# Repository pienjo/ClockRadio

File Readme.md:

This is just a simple alarm clock.

How to use
==========

## Main display

A short press on the mode button rotates between the following modes:

  * Time. The first 2 columns of the LED display are used for a Day-of-week indicator; monday is at the first row.
  * Date
  * Alarm 1.  
  * Alarm 2. 
  * One-time alarm

A long press on the mode button will edit whatever is being displayed (time,
alarm 1, alarm 2, or one-time alarm). Performing a long press while the
date is being shown will edit the time drift compensation. The display will
return to ''Time'' when no buttons are pressed.

## Display brightness

The display has separate brightness settings for day and night. Transition 
from day to night occurs roughly around sunrise (Assuming a northern 
lattitude of aroudn 51 degrees). 

Brightness can be changed using the ''increase'' and ''decrease'' buttons while the 
display is showing the time.

## Daylight saving time

The clock will automatically apply daylight saving time, based on the current (2019) 
EU rules (which are bound to change again, oh well)

## Editing

A short press on the mode button will advance to the next digit/number. Use 
the increment/decrement buttons to change digits/numbers. A long press
on the mode button will abort the edit.

## Radio

Pressing the on/off button will toggle the radio. When the radio is active,
the "Time" page will show the tuned frequency instead. When the radio is on,
the "Increase" and "Decrease" can be used for tuning. A short press on either
button will do a manual tune, a long press will perform an automatic seek for
the next channel.

To change the volume of the radio, hold down the on/off button and use the
increase/decrease buttons for volume control.

## Alarm

There are 2 regular alarms. They can sound on weekdays, on weekends, or both. 
They can be edited by doing a long-press on the mode button while the relevant
alarm is being displayed.

To disable or enable an alarm, press the ''on/off'' button while the alarm is
being displayed. Press the ''increment'' button to silence only the upcoming
invocation of the alarm. I added this because I often wake up before the
alarm is set to sound; in these cases I want to disable the alarm for today, 
but it should still arm itself for tomorrow without me having to remember
doing so...

Alarms can either turn on the radio, or turn on the beeper. While an alarm is
active, any button can be used to disable the alarm (the regular function of
the buttons is disabled while an alarm is active). When an alarm is scheduled
to go off while the previous alarm is still active, the first alarm is 
automatically silenced. (for example: my first alarm turns on the radio at
6:55 so I can listen to the news. If I'm not out of bed by 7:10, the second
alarm will sound the beeper).

Alarms will automatically be disabled after a certain timeout (1 hour for
radio alarms, 4 minutes for beeper alarms).

There is also a one-time alarm, for those times where you need to wakeup
at a non-standard hour. It behaves the same as the normal alarms, but doesn't
re-arm itself.

## sleep/nap

There is a sleep- or naptimer, sharing a single button. When the radio is
turned on while the sleep/nap button is pressed, the sleep function activates.
Press the button repeatedly to change the desired sleep interval. The radio
will turn off after this time.

If the radio was turned off when the sleep/nap button was pressed, the nap
function activates. It will sound the beeper alarm once the nap timer has 
expred. Press the sleep/nap button repeatedly to change the desired nap 
interval.

Both sleep and nap timers have a '':00'' interval - Selecting this interval
will disable the sleep/nap timer.

Hardware
========

Unfortunately, I lost the schematics for this clock. It was kind of cobbled
together at the spot. I'll include an overview, which should be enough to 
recreate a suitable schematic.

## Buttons

There are 5 switches, which pull down to GND:
 
  * **mode** (''BUTTON_1'', connected to PD0)
  * **on/off** (''BUTTON_2'', connected to PD1) 
  * **decrease** (''BUTTON_3'', connected to PD3)
  * **increase** (''BUTTON_4'', connected to PD4)
  * **sleep/nap** (''BUTTON_5'', connected to PD5)

There is **no** button connected to PD2 (ex0). Instead, it is connected to the
clock output of the DS1307. This will generate ''CLOCK_UPDATE'' events.

## Display 

The display consists of 4 MAX7219 modules from AliExpress. They came with an
8x8 LED matrix, and are connected in cascade (DOUT connected to DIN of the next
module. SCK is shared among all modules). 

They are configured over SPI, and use the hardware SPI module of the AVR:

  * MOSI (PB3 of the AVR) is connected to DIN of the first module.
  * SCK (PB5 of the AVR) is connected to CLK of the first module.
  * PB2 is connected to LOAD(/CS) of the first module.

I replaced the 8x8 matrix of the last module with a 4x7 segment display
plus some status LEDs on an adapter board. See the "schematics" in 
Hardware/display ) Note that the 4x7 segment that I happened to find in my
parts bin was common anode rather than common cathode!

## FM Radio

The clock uses an SI4702 radio module. **This module must be supplied with
3.3V**. I used an XC6206 low-dropout regulator.

The module is configured over I2C, using the hardware I2C module (SDA at PC4,
SCL at PC5). These need to be level-shifted because of difference in supply
voltage - I used a standard BSS138 based level shifter. See 
Hardware/levelshifter .

In addition, the reset line of the SI4702 module is connected to PC3. It 
doesn't need a level shifter; the AVR will only pull this low during the
power-up of the FM radio.

The outputs of the SI4702 need to be decoupled using a suitably large 
capacitor (I think I used a 10 uF electrolytic) because of different biasing.

## Beeper 

PC1 is used to generate a crude beeper. It is connected to the input of the
audio amplifier, using a potentiometer (for volume control) and a small
decoupling capacitor.

## Audio amplifier

I used a cheap amplifier module from AliExpress (LM386-based), connected to
4 small (29mm) speakers, .25W @ 8 Ohm, connected in two parallel chains of
2 (for a total impedance of 8 Ohm).

Since this amplifier turned out to be rather noisy, I added a PNP transistor
to its supply line, so it can be turned off if the radio and beeper are 
quiet. This transistor is controlled by PC2.

Building
========

You need to have the following installed:

  * A recent version of gcc-avr 
  * A recent version of avr-libc
  * avrdude for programming. The TX and RX lines are in use, so it's
    probably best to use an ISP programmer.
  * lua (5.1 or 5.2) to generate the bitmap- and font code.

To run the unittests in tests, you'll also need simavr plus its headers.

Case
====

I posted the case I made for this alarm clock to Thingiverse, see 

https://www.thingiverse.com/thing:3313125

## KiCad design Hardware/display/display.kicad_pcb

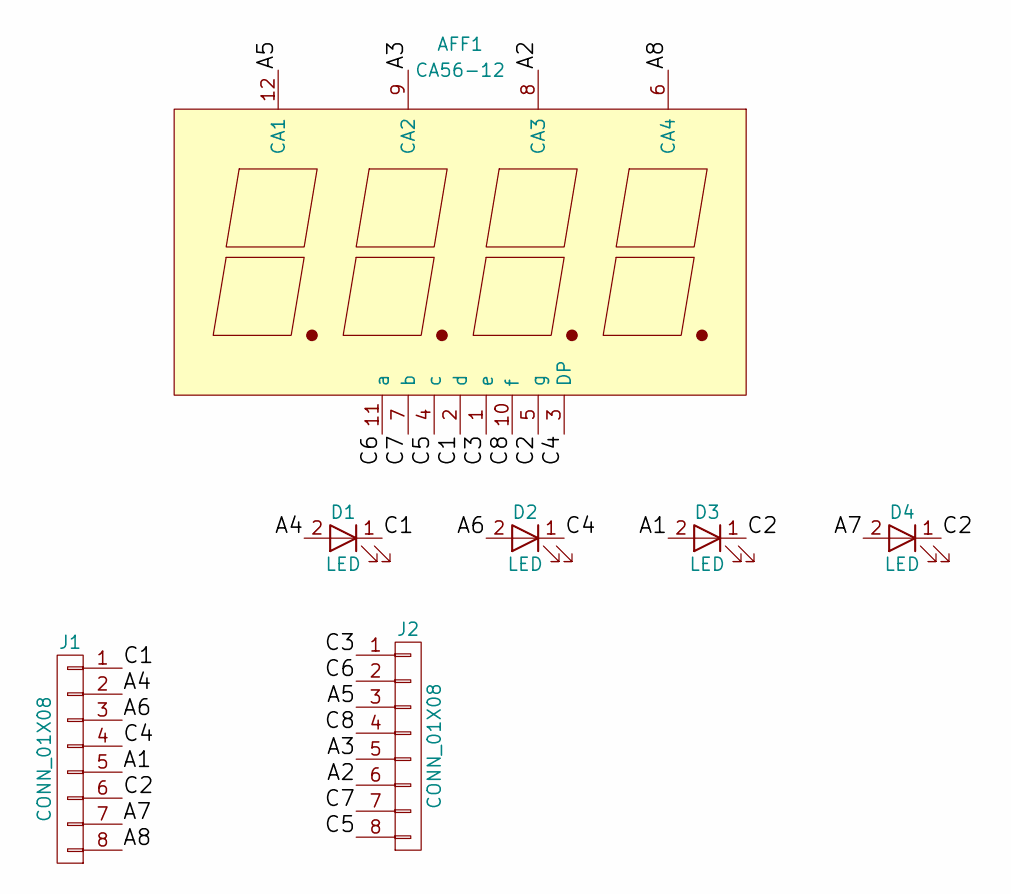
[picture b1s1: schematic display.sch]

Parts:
AFF1: CA56-12; SMA413064
D1, D2, D3, D4: LED; LED_D5.0mm
J1, J2: CONN_01X08; Pin_Header_Straight_1x08_Pitch2.54mm

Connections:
/A1: D3.2 (A), J1.5
/A2: AFF1.8 (CA3), J2.6
/A3: AFF1.9 (CA2), J2.5
/A4: D1.2 (A), J1.2
/A5: AFF1.12 (CA1), J2.3
/A6: D2.2 (A), J1.3
/A7: D4.2 (A), J1.7
/A8: AFF1.6 (CA4), J1.8
/C1: AFF1.2 (d), D1.1 (K), J1.1
/C2: AFF1.5 (g), D3.1 (K), D4.1 (K), J1.6
/C3: AFF1.1 (e), J2.1
/C4: AFF1.3 (DP), D2.1 (K), J1.4
/C5: AFF1.4 (c), J2.8
/C6: AFF1.11 (a), J2.2
/C7: AFF1.7 (b), J2.7
/C8: AFF1.10 (f), J2.4

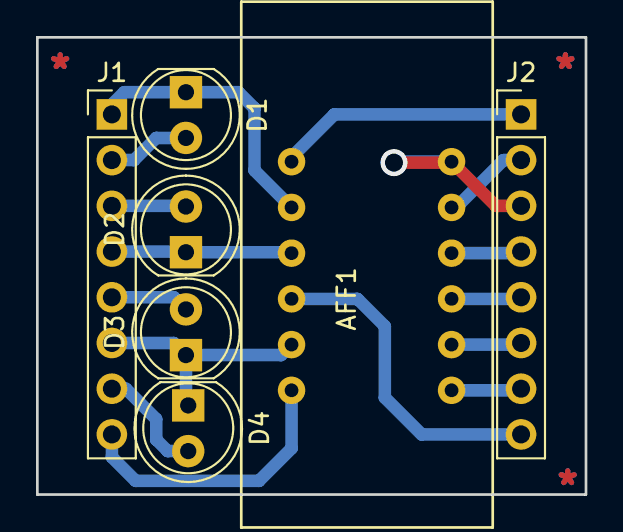
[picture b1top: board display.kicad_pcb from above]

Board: 2 copper layers, 30.5 x 25.4 mm, 7 parts (0 on the bottom side), 16 nets.

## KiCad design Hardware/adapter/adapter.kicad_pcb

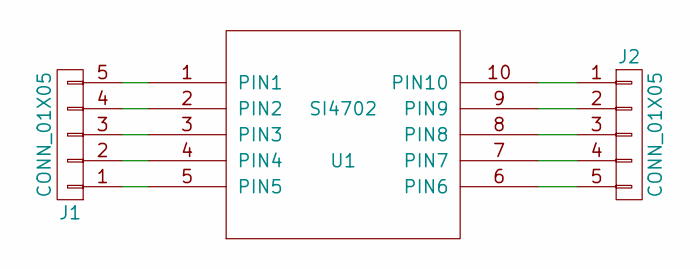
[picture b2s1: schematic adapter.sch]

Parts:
J1, J2: CONN_01X05; Pin_Header_Straight_1x05_Pitch2.54mm
U1: SI4702; mvb_SI4702

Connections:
unnamed: J1.1, U1.5 (PIN5)
unnamed: J1.2, U1.4 (PIN4)
unnamed: J1.3, U1.3 (PIN3)
unnamed: J1.4, U1.2 (PIN2)
unnamed: J1.5, U1.1 (PIN1)
unnamed: J2.1, U1.10 (PIN10)
unnamed: J2.2, U1.9 (PIN9)
unnamed: J2.3, U1.8 (PIN8)
unnamed: J2.4, U1.7 (PIN7)
unnamed: J2.5, U1.6 (PIN6)

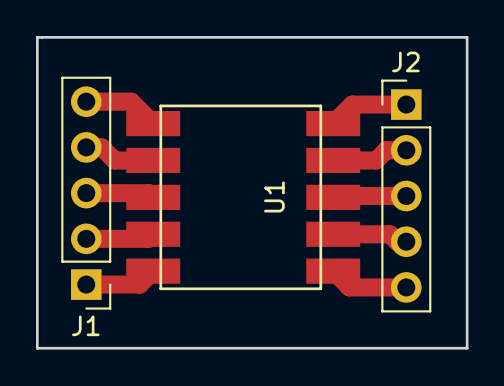
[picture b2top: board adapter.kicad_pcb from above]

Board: 2 copper layers, 23.9 x 17.3 mm, 3 parts (0 on the bottom side), 10 nets.

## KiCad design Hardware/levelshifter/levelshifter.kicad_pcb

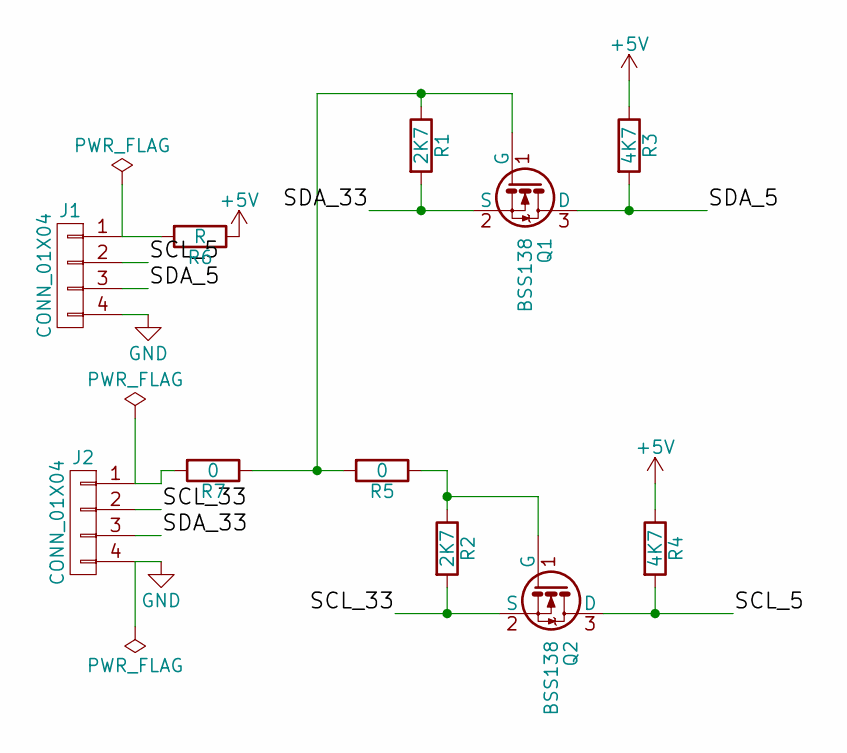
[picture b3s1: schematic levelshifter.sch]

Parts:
J1, J2: CONN_01X04; Pin_Header_Straight_1x04_Pitch2.54mm
Q1, Q2: BSS138; SOT-23_Handsoldering
R1, R2: 2K7; R_0603_HandSoldering
R3, R4: 4K7; R_0603_HandSoldering
R5: 0; R_Axial_DIN0204_L3.6mm_D1.6mm_P5.08mm_Horizontal
R6: R; R_Axial_DIN0204_L3.6mm_D1.6mm_P5.08mm_Horizontal
R7: 0; R_Axial_DIN0204_L3.6mm_D1.6mm_P7.62mm_Horizontal

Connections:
+5V: R3.1, R4.1, R6.1
/SCL_5: J1.2, Q2.3 (D), R4.2
/SCL_33: J2.2, Q2.2 (S), R2.2
/SDA_5: J1.3, Q1.3 (D), R3.2
/SDA_33: J2.3, Q1.2 (S), R1.2
GND: J1.4, J2.4
unnamed: J1.1, R6.2
unnamed: J2.1, R7.2
unnamed: Q1.1 (G), R1.1, R5.2, R7.1
unnamed: Q2.1 (G), R2.1, R5.1

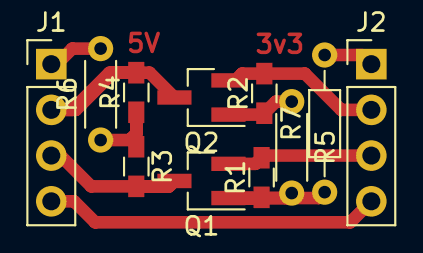
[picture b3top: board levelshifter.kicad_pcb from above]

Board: 2 copper layers, 11 parts (0 on the bottom side), 10 nets.

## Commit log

2017-03-21 Before I kill it
2017-03-21 Add font creation
2017-03-22 Rolling display
2017-03-25 It actually shows something
    * Created crude rendering engine
    * Fixed font
2017-03-31 Don't use a frame buffer, just compose lines individually
2017-03-31 Use time from DS1307
2017-04-06 Migrate to target board - which turns out to have an ATMega 168p instead :(
2017-04-06 Extensive changes
    * Moved DS1307 code to separate .c file
    * Moved SPI initialisation there
    * Use a timer for the animation ticks
    * Configure the DS1307 to use a 1-sec timer, use that to wake up the cpu
    * Put CPU to sleep between updates
    * Add a 4th panel, featuring 4 7-segment displays.
2017-04-06 Don't perform animation loop when only the 7-segment display changed
2017-04-11 Started button handling
2017-04-13 Add blinking digits
2017-04-20 Inefficient: Adjust date.
2017-08-02 Unfinished, but want to continue on shiny
2017-08-02 from shiny
2017-08-07 Allow to seek up and down
2017-08-07 Renderer: Show horizontal dashes when radio disabled
2017-08-07 Enable crude radio. Only tuning, no repeat, no seek. Remove special treatment of the clock signal - there's no need for an external EXT0 handler.. Correctly implement disabling of radio.
2017-08-26 Improve listfile format
2017-08-26 Add macros for LEDs.
2017-08-26 Implement seeking Improve volume handling
2017-08-26 Add support for status LEDs. Add volume viewing
2017-08-26 Re-implement state machine. Implement seeking and volume control
2017-08-31 * Add key repeat * Add brightness control
2017-09-03 PCB for display adapter
2017-09-03 Only pull down RESET line, don't pull it up. Prevents overloading the ESD diodes of the radio chip..
2017-09-03 Implement alarm beeper.
2017-09-03 What is this doing here?
2017-09-04 Fixed column of leds
2017-09-04 Fix missing include
2017-09-04 Change setting storage: * Add 2 alarms * Implement CRC checking to detect lost data * Show the two alarms. * Use a timer to write settings.
2017-09-06 Allow editing of alarms. Problem: No flash mask for days.
2017-09-06 * Enable flashing for day-of-week indicator * Enable cancel and timeout for alarm setting
2017-09-07 Change rendering of alarm. Fixes setting of alarm
2017-09-07 Fix mode cycling
2017-09-14 Fix alarm editing
2017-09-16 Improve blinking behaviour
2017-09-16 Implement alarm triggering
2017-09-30 Add characters for "NAP" and "SLEEP". The latter will be 1 dot too wide
2017-09-30 Come to think of it, make font spacing consistent, and let the rendering deal with squeezing in "Sleep" on a display that is 1 pixel too short
2017-09-30 Added annotation to font generation
2017-09-30 Fix font generation, don't explicitly specify array length
2017-09-30 Fix list generation, and remove it during a clean
2017-10-01 Nap- and sleep timer
2017-10-01 Don't use the font to generate bitmaps, use bitmaps instead.
2017-10-01 Improve bitmaps, improve build order
2017-10-01 Added 2 more LEDs
2017-10-08 Finalized 7-segment adapter board.
2017-10-08 Added copper layout
2017-10-08 Use all 4 LEDs
2017-10-15 Ignore listfile
2017-10-15 Add DST handling
    Known issue: DST switch not handled when clock is running on backup
2017-10-15 Apply DST change after power recovery.
    Untested.
2017-10-15 Re-try reset of SI4702 if it doesn't respond.
2017-10-15 Improve time setting
    * Keep updating the time when setting the date.
    * Keep updating the second register when setting the time.
    * Allow the second register to be reset
    * Don't write the second register when done setting time. This
    avoid resetting the second divider
2018-04-05 Fix build (??)
2018-04-05 Revert "Improve time setting"
    This reverts commit 912c0d4aaa939b37706aa454e5420bd57b75260c.
2018-04-05 Revert "Apply DST change after power recovery."
    This reverts commit f36825cdc5ec0c8c8f84a6f0239469cbc25ce133.
2018-04-05 Revert "Add DST handling"
    This reverts commit f66c807ea54dc31d3d43feee1b297fb95b94a05c.
2018-04-06 Re-implemented DST.
    Day-of-week calculation appears incorrect, time for some unit tests
2018-04-06 Fix gitignore
2018-04-06 Add "unittests" , for use with simavr
2018-04-06 Fix some of the bugs in TimeFuncs
2018-04-07 Separated BCD functions to separate file, add more tests.
    Fixed several newly discovered bugs in timefuncs :(
2018-04-07 Use BCD routines for adjusting clock
2018-04-07 Write tests for NormalizeHours + fix
2018-04-07 Expose IsDstActive() for test
2018-04-07 Add tests for IsDSTActive (No bugs, yay)
2018-04-07 Bugsquash
    Fix warnings from cppcheck.
    Fix alarm time checking
2018-04-07 Auto-switch brightness
2018-04-08 Propagate test target
2018-04-08 Create tests for brightness setting routines
2018-04-08 Fix off-by-one in "ItIsDarkOutside"
2018-04-08 Only update screen when something actually changed. Reduces noise on the radio when tuned to a weak station
2018-04-10 Disable animations while the radio is on
2018-04-10 Fix cache: Also include secondary screen
2018-04-10 Rewrite alarm handling; separate clock events from timing events
2018-04-10 Fix (?) I2C instability, rewrite SI4702 register layout
2018-04-13 Repair handling of longpresses
2018-04-13 Limit amount of recovery attempts
2018-04-13 Fall back to beeper if radio cannot be started
2018-04-15 Fix day-of-week rollover
    also fix tests
2018-04-15 Failing to ack I2C data is a failure
2018-04-20 Always re-initialize SI4702 when powering it on
2018-04-20 Enable watchdog
2018-04-20 Add support for inverted display
2018-04-20 Invert screen when radio alarm is firing, instead of blinking.
2018-04-23 Allow next invocation of alarm to be suspended
2018-04-23 Sacrifice separation between "Sleep" and "Nap", add a third alarm
2018-11-08 Added time adjust to settings + rendering
2018-11-12 Fix display of time adjust, actually implement adjustment
2018-11-13 Misc bugfix
    * Move edit handling to BCDFuncs, add unittests, fix bugs.
    * Fix time adjustment BCD bug
    * obliterate data segment size of tests.
2018-12-25 Add output directory as a dependency
2018-12-29 oops
2018-12-29 Remove dead case
2018-12-29 Add license agreement
2018-12-30 Improve makefile
2018-12-30 Added a readme
2018-12-30 Create LICENSE
2019-11-30 Improve panel robustness by re-initializing on every write
2019-11-30 Add AVR IspMK2 programmer
